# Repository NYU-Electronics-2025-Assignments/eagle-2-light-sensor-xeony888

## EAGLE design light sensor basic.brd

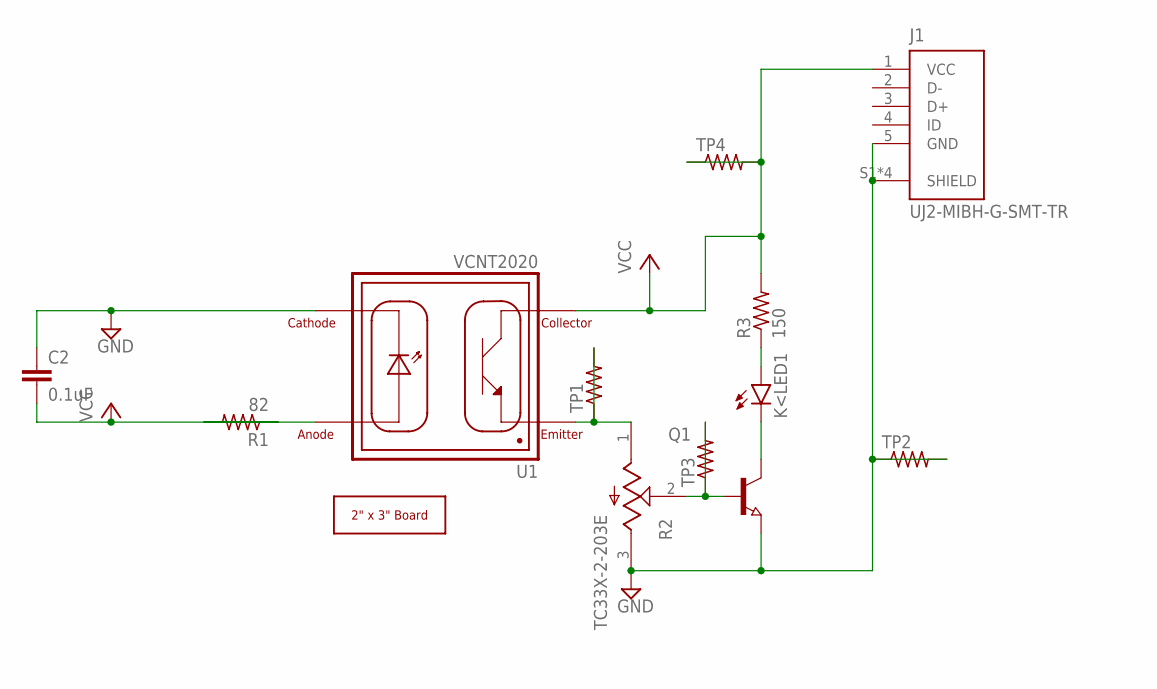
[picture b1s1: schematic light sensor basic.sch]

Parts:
C2: 0.1uF; C1206
J1: UJ2-MIBH-G-SMT-TR; CUI_UJ2-MIBH-G-SMT-TR
K<LED1: LEDCHIPLED_0805; CHIPLED_0805
Q1: NPN-TRANSISTOR_SOT23; SOT23
R1: 82; R1206
R2: TC33X-2-203E; TRIM_TC33X-2-203E
R3: 150; R0805
TP1, TP2, TP3, TP4: R-US_R1206; R1206
U1: VCNT2020; XDCR_VCNT2020
U$1: 2X3_BOARD_V2

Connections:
GND: C2.1, J1.5 (GND), J1.S1 (SHIELD), J1.S2 (SHIELD), J1.S3 (SHIELD), J1.S4 (SHIELD), Q1.2 (E), R2.3 (CW), TP2.1, TP2.2, U1.4 (CATHODE)
unnamed: R1.2, U1.3 (ANODE)
unnamed: K<LED1.C, Q1.3 (C)
unnamed: R2.1 (CCW), TP1.1, TP1.2, U1.1 (EMITTER)
unnamed: K<LED1.A, R3.1
unnamed: Q1.1 (B), R2.2 (W), TP3.1, TP3.2
VCC: C2.2, J1.1 (VCC), R1.1, R3.2, TP4.1, TP4.2, U1.2 (COLLECTOR)

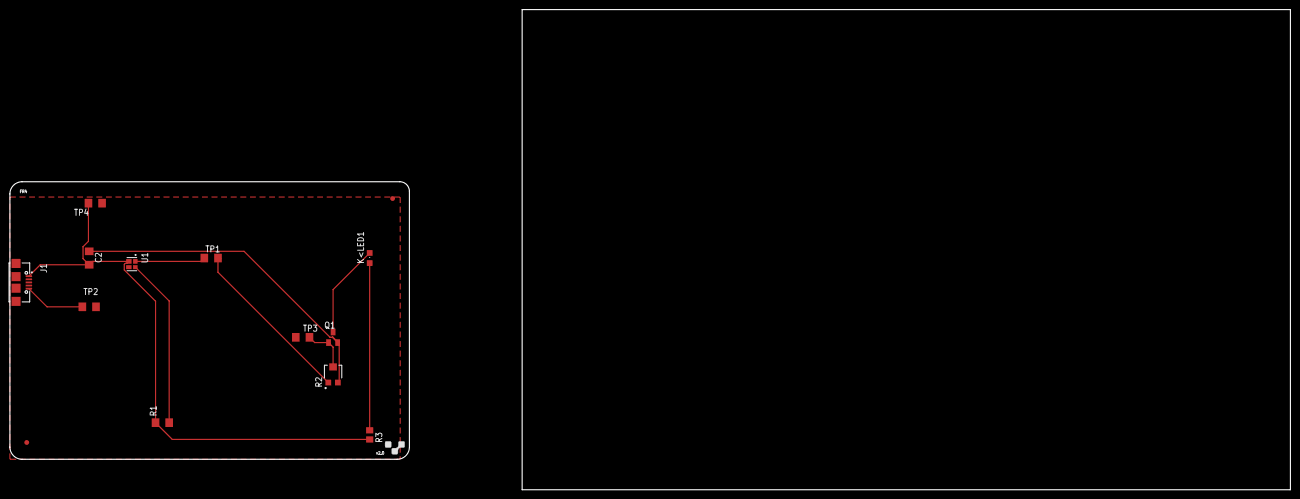
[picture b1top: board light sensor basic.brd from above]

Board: 2 copper layers, 83.2 x 57.8 mm, 13 parts (0 on the bottom side), 7 nets.

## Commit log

2025-05-10 Finished
